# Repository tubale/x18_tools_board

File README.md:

# ROV Tools Board

A custom **4-layer STM32-based PCB** designed for Purdue IEEE Underwater Robotics to control a six-servo robotic arm. This project involved the complete hardware development cycle, including system architecture, schematic design, PCB layout, power distribution, board bring-up, debugging, and integration into the ROV.

---

## Overview

The Tools Board serves as the interface between the Raspberry Pi and the ROV's robotic arm. It provides reliable power delivery, real-time servo control, and SPI communication while operating in a high-current, electrically noisy environment.

This project was designed from the ground up using KiCad and assembled, tested, and validated on the team's underwater robot.

---

## Features

- Custom **4-layer PCB** designed in **KiCad**
- **STM32 microcontroller** for real-time control
- Controls **6 independent servo motors**
- Supports up to **4A peak current**
- High-efficiency **12V → 6V buck converter**
- **5V → 3.3V LDO** for the STM32 and logic circuitry
- **SPI communication** with Raspberry Pi
- Optimized PCB layout with isolated power planes for improved signal integrity
- Hand assembled and fully validated through hardware bring-up

---

## Hardware Architecture

```text
                 Raspberry Pi
                      │
                   SPI Interface
                      │
              ┌───────────────┐
              │   STM32 MCU   │
              └───────────────┘
          PWM │ │ │ │ │ │
              ▼ ▼ ▼ ▼ ▼ ▼
        ┌────────────────────┐
        │   6 Servo Outputs  │
        └────────────────────┘

12V Input
    │
    ▼
┌──────────────┐
│ Buck 12V→6V  │────────► Servos
└──────────────┘
    │
    ▼
┌──────────────┐
│ LDO 5V→3.3V  │────────► STM32 + Logic
└──────────────┘
```

---

## Design Process

### System Architecture

- Defined power and communication requirements
- Selected STM32 microcontroller
- Designed SPI interface with Raspberry Pi
- Planned high-current power distribution for servo operation

### Schematic Design

Designed the complete electrical schematic including:

- STM32 microcontroller
- Servo outputs
- SPI interface
- Programming/debug connector
- Buck converter
- LDO regulator
- Decoupling and filtering circuitry
- Status LEDs
- Connectors

### PCB Layout

Designed a **4-layer PCB** with:

- Dedicated ground plane
- Dedicated power plane
- High-current routing for servo power
- Short SPI signal paths
- Proper decoupling placement
- Separation between noisy power circuitry and sensitive digital signals

### Assembly

- Soldered surface-mount and through-hole components
- Inspected and verified board assembly
- Performed continuity testing before power-up

### Bring-Up & Validation

Verified each subsystem independently using:

- Digital Multimeter
- Oscilloscope
- Logic Analyzer

Testing included:

- Power rail verification
- SPI communication
- PWM generation
- Servo functionality
- Current measurements
- Signal integrity

---

### Technologies

**Hardware:** KiCad • STM32 • SPI • PWM • 4-Layer PCB Design • Buck Converter Design • LDO Voltage Regulation

**Testing:** Oscilloscope • Logic Analyzer • Digital Multimeter

---

## Gallery

### Schematic

### Layout

### Assembled Board

---

## Author

**Tanay Ubale**

Electrical & Computer Engineering Student at Purdue University

Interested in Digital Design, FPGA Development, ASIC Design, Embedded Systems, PCB Design, and Computer Architecture.

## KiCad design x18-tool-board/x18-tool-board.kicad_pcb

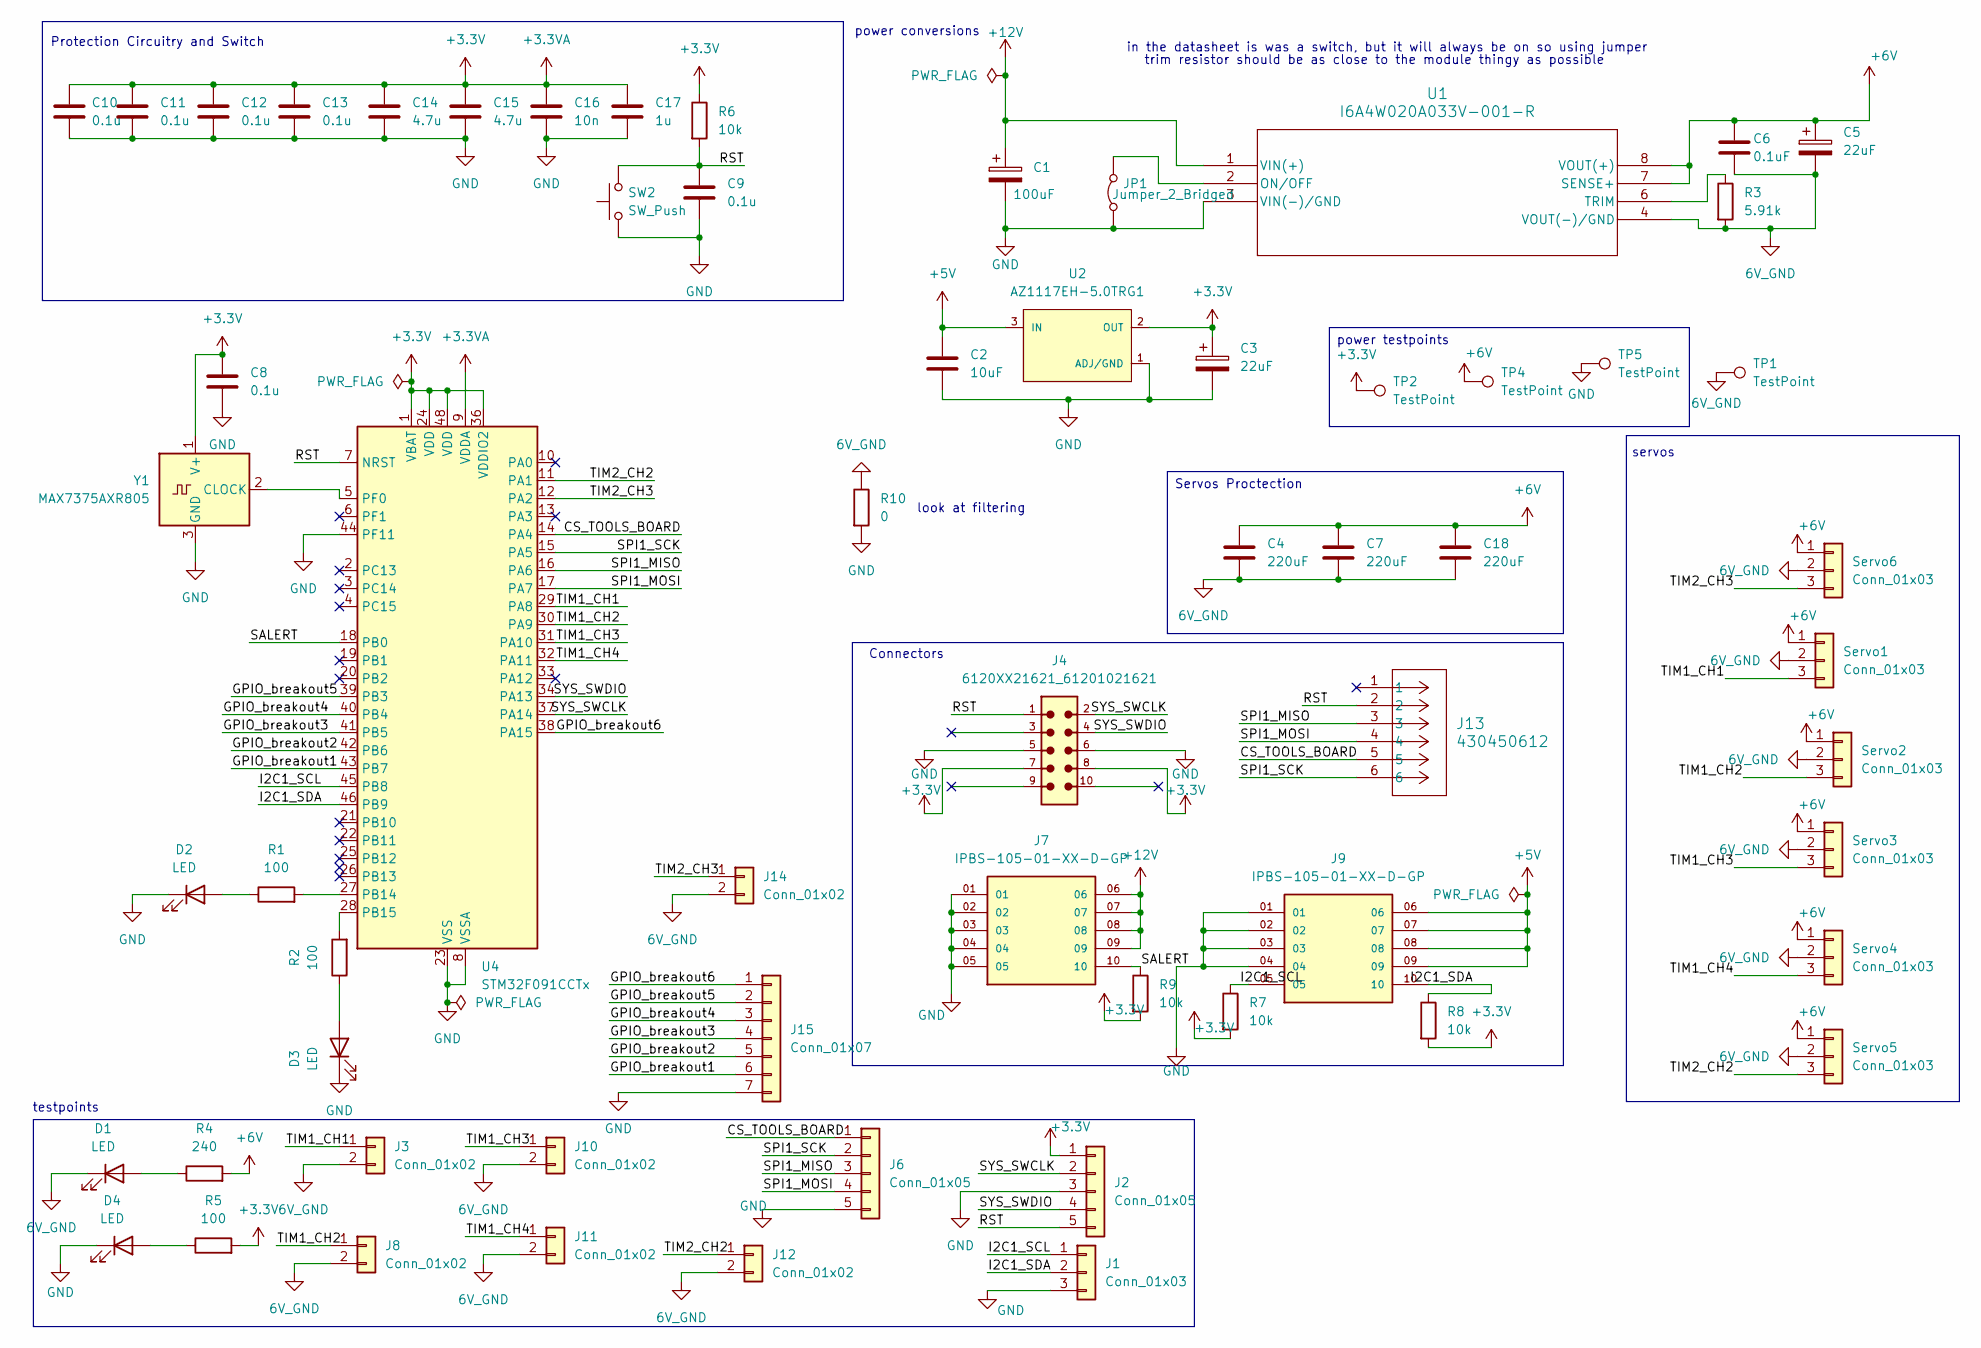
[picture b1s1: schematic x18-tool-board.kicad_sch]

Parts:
C1: 100uF; CAPMP7.6X4.3_4.3N_KEM-L
C2: 10uF; C_0603_1608Metric_Pad1.08x0.95mm_HandSolder
C3, C5: 22uF; C_0603_1608Metric_Pad1.08x0.95mm_HandSolder
C4, C7, C18: 220uF; U2-K_NCH-M
C6: 0.1uF; C_0603_1608Metric_Pad1.08x0.95mm_HandSolder
C8, C9, C10, C11, C12, C13: 0.1u; C_0603_1608Metric_Pad1.08x0.95mm_HandSolder
C14, C15: 4.7u; C_0603_1608Metric_Pad1.08x0.95mm_HandSolder
C16: 10n; C_0603_1608Metric_Pad1.08x0.95mm_HandSolder
C17: 1u; C_0603_1608Metric_Pad1.08x0.95mm_HandSolder
D1, D2, D3, D4: LED; LED_0805_2012Metric_Pad1.15x1.40mm_HandSolder
J1: Conn_01x03; PinHeader_1x03_P2.54mm_Vertical
J2, J6: Conn_01x05; PinHeader_1x05_P2.54mm_Vertical
J3, J8, J10, J11, J12, J14: Conn_01x02; PinHeader_1x02_P2.54mm_Vertical
J4: 6120XX21621_61201021621; 61201021621
J7, J9: IPBS-105-01-XX-D-GP; SAMTEC_IPBS-105-01-XX-D-GP; PARTREV M
J13: 430450612; CONN_SD-43045-005_06_MOL
J15: Conn_01x07; PinHeader_1x07_P2.54mm_Vertical
JP1: Jumper_2_Bridged; SolderJumper-2_P1.3mm_Bridged_Pad1.0x1.5mm
R1, R2, R5: 100; R_0603_1608Metric_Pad0.98x0.95mm_HandSolder
R3: 5.91k; R_0603_1608Metric_Pad0.98x0.95mm_HandSolder
R4: 240; R_0603_1608Metric_Pad0.98x0.95mm_HandSolder
R6, R7, R8, R9: 10k; R_0603_1608Metric_Pad0.98x0.95mm_HandSolder
R10: 0; R_0805_2012Metric_Pad1.20x1.40mm_HandSolder
SW2: SW_Push; SW_FSM2JMTR_TEC-M
Servo1, Servo2, Servo3, Servo4, Servo5, Servo6: Conn_01x03; CUI_TB006-508-03BE
TP1, TP2, TP4, TP5: TestPoint; TestPoint_Pad_D4.0mm
U1: I6A4W020A033V-001-R; i6A_TDK
U2: AZ1117EH-5.0TRG1; SOT-223_DIO
U4: STM32F091CCTx; LQFP-48_7x7mm_P0.5mm
Y1: MAX7375AXR805; SOT-323_SC-70

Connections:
6V_GND: C4.2, C5.2, C6.2, C7.2, C18.2, D1.1 (K), J3.2, J8.2, J10.2, J11.2, J12.2, J14.2, R3.2, R10.1, Servo1.2, Servo2.2, Servo3.2, Servo4.2, Servo5.2, Servo6.2, TP1.1, U1.4 (VOUT(-)/GND)
+3.3V: C3.1, C8.1, C10.1, C11.1, C12.1, C13.1, C14.1, C15.1, C16.1, C17.1, J2.1, J4.7, J4.8, R5.2, R6.1, R7.2, R8.2, R9.2, TP2.1, U2.2 (OUT), U2.4 (OUT), U4.1 (VBAT), U4.9 (VDDA), U4.24 (VDD), U4.36 (VDDIO2), U4.48 (VDD), Y1.1 (V+)
+5V: C2.1, J9.06, J9.07, J9.08, J9.09, U2.3 (IN)
+6V: C4.1, C5.1, C6.1, C7.1, C18.1, R4.2, Servo1.1, Servo2.1, Servo3.1, Servo4.1, Servo5.1, Servo6.1, TP4.1, U1.7 (SENSE+), U1.8 (VOUT(+))
+12V: C1.1, J7.06, J7.07, J7.08, J7.09, U1.1 (VIN(+))
/CS_TOOLS_BOARD: J6.1, J13.5, U4.14 (PA4)
/GPIO_breakout1: J15.6, U4.43 (PB7)
/GPIO_breakout2: J15.5, U4.42 (PB6)
/GPIO_breakout3: J15.4, U4.41 (PB5)
/GPIO_breakout4: J15.3, U4.40 (PB4)
/GPIO_breakout5: J15.2, U4.39 (PB3)
/GPIO_breakout6: J15.1, U4.38 (PA15)
/I2C1_SCL: J1.1, J9.05, R7.1, U4.45 (PB8)
/I2C1_SDA: J1.2, J9.10, R8.1, U4.46 (PB9)
/RST: C9.1, J2.5, J4.1, J13.2, R6.2, SW2.2, U4.7 (NRST)
/SALERT: J7.10, R9.1, U4.18 (PB0)
/SPI1_MISO: J6.3, J13.3, U4.16 (PA6)
/SPI1_MOSI: J6.4, J13.4, U4.17 (PA7)
/SPI1_SCK: J6.2, J13.6, U4.15 (PA5)
/SYS_SWCLK: J2.2, J4.2, U4.37 (PA14)
/SYS_SWDIO: J2.4, J4.4, U4.34 (PA13)
/TIM1_CH1: J3.1, Servo1.3, U4.29 (PA8)
/TIM1_CH2: J8.1, Servo2.3, U4.30 (PA9)
/TIM1_CH3: J10.1, Servo3.3, U4.31 (PA10)
/TIM1_CH4: J11.1, Servo4.3, U4.32 (PA11)
/TIM2_CH2: J12.1, Servo5.3, U4.11 (PA1)
/TIM2_CH3: J14.1, Servo6.3, U4.12 (PA2)
GND: C1.2, C2.2, C3.2, C8.2, C9.2, C10.2, C11.2, C12.2, C13.2, C14.2, C15.2, C16.2, C17.2, D2.1 (K), D3.1 (K), D4.1 (K), J1.3, J2.3, J4.5, J4.6, J6.5, J7.01, J7.02, J7.03, J7.04, J7.05, J9.01, J9.02, J9.03, J9.04, J15.7, JP1.1 (A), R10.2, SW2.1, TP5.1, U1.3 (VIN(-)/GND), U2.1 (ADJ/GND), U4.8 (VSSA), U4.23 (VSS), U4.35 (VSS), U4.44 (PF11), U4.47 (VSS), Y1.3 (GND)
unnamed: D1.2 (A), R4.1
unnamed: D2.2 (A), R1.1
unnamed: D3.2 (A), R2.1
unnamed: D4.2 (A), R5.1
unnamed: JP1.2 (B), U1.2 (ON/OFF)
unnamed: R3.1, U1.6 (TRIM)
unnamed: R1.2, U4.27 (PB14)
unnamed: R2.2, U4.28 (PB15)
unnamed: U4.5 (PF0), Y1.2 (CLOCK)

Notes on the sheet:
testpoints
servos
in the datasheet is was a switch, but it will always be on so using jumper
power conversions
trim resistor should be as close to the module thingy as possible
Connectors
look at filtering
Protection Circuitry and Switch
Servos Proctection
power testpoints

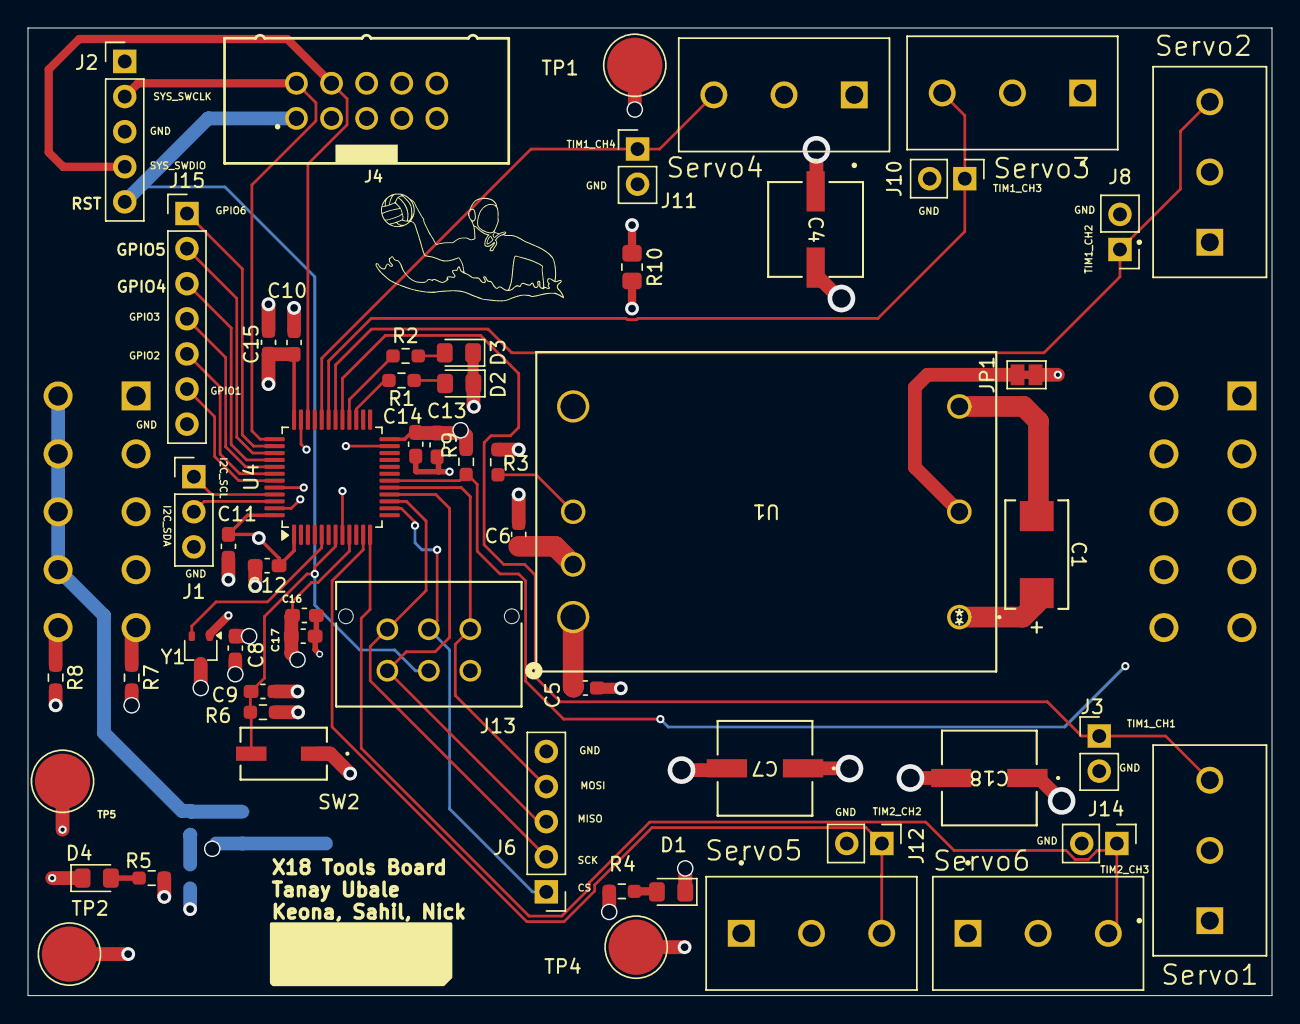
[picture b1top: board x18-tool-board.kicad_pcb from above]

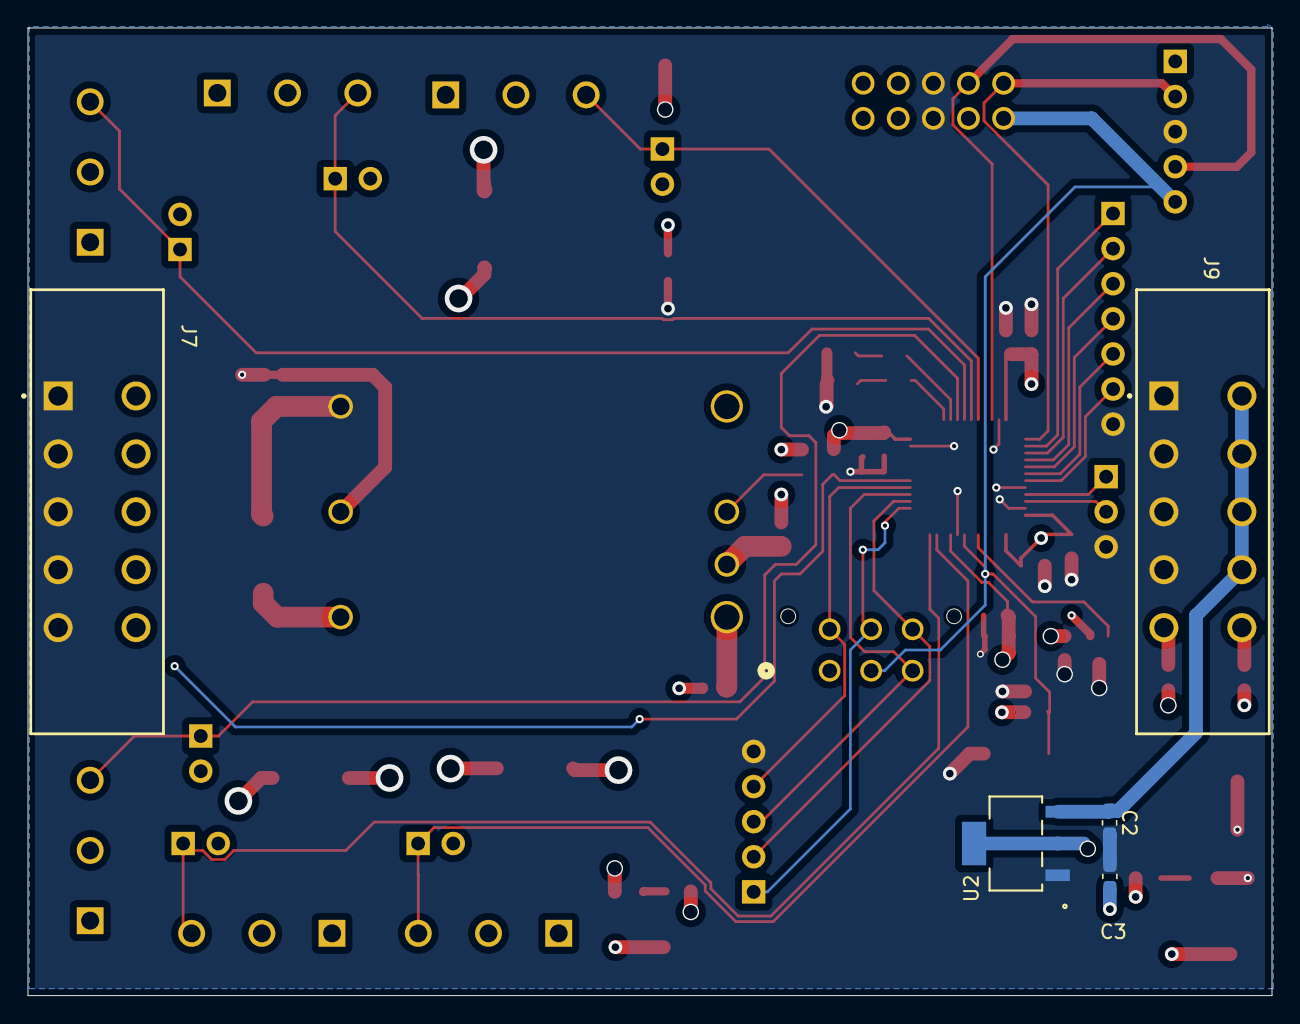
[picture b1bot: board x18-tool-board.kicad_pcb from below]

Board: 4 copper layers, 90.0 x 70.0 mm, 62 parts (5 on the bottom side), 37 nets.
